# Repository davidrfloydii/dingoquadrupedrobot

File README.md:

# dingoquadrupedrobot
Modifications to Dingo Quadruped Robot

## [KiCAD PCB](https://github.com/davidrfloydii/dingoquadrupedrobot/tree/main/PCB)
Since the original files were Altium designer I recreated the board in KiCAD. Not 100% the same since it uses through hole components for the resistors and the diode.

## [Modified Base Plate](https://github.com/davidrfloydii/dingoquadrupedrobot/blob/main/CAD/Dingo%20Base%20Plate.step)
Instead of ordering the Acrylic pieces you can try to print your own base plates. **Note**: This is not verified to hold up to the stresses of the robot. However if you decide to go this route be sure to use 100% infill for these pieces. Also blue the two halves together. Since it is printed this will have stand offs for 2 of the Raspberry Pi mounts and the rear of the front buck converter.

## [Redesigned LCD Bracket](https://github.com/davidrfloydii/dingoquadrupedrobot/blob/main/CAD/Rear%20LCD%20Holder%20v1.step)
For my build I decided to redesign the rear LCD holder so that screws and nuts weren't positioning. **Note** This still has not been tested and results may vary depending on your printer settings.

## [New nose piece](https://github.com/davidrfloydii/dingoquadrupedrobot/blob/main/CAD/Dingo%20Front%20With%20Sonar%20v1.step)
The first modificaiton was to the front of the Dingo robot, it removes the plastic black eye and instead makes room for two HC-SR04 sensors.

## [New Fan Housing](https://github.com/davidrfloydii/dingoquadrupedrobot/blob/main/CAD/Fan%20Housings%20Builtin%20Hinge%20Pins.step)
This new fan housing creates tabs to act as the hinge. Reduces the number of pieces that need to be ordered.

## [Revised IMU Mount]((https://github.com/davidrfloydii/dingoquadrupedrobot/blob/main/CAD//Revised%20IMU%20Mount%20v4.step)
I updated the IMU mount because the version I ordered here in the US had slightly different pattern for mounting holes. Additionally the 3 digit display I ordered from Amazon also had slightly different mounting holes. If you are using the same components you can use this step file.

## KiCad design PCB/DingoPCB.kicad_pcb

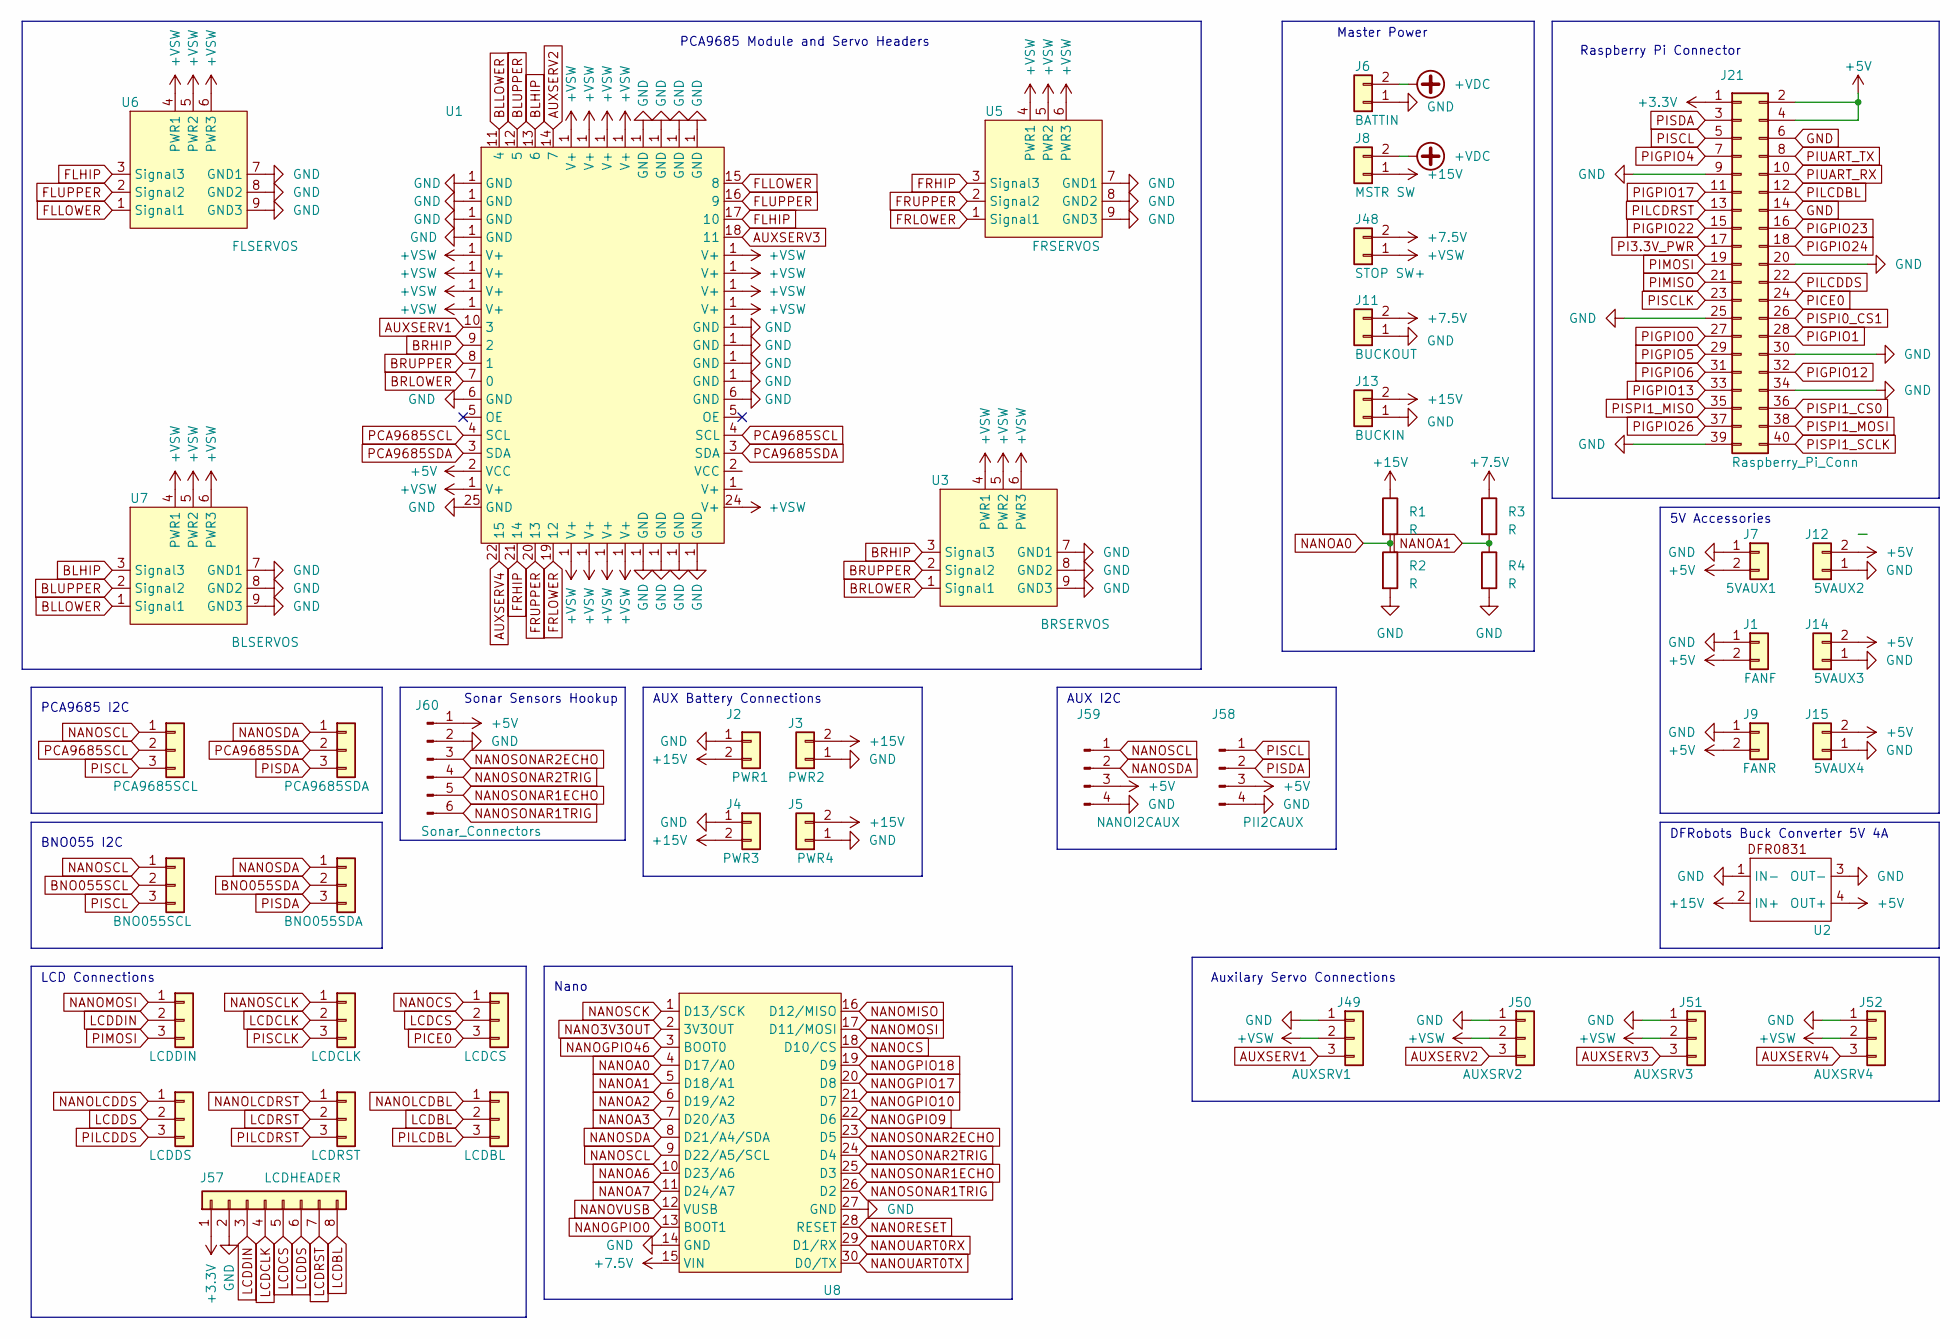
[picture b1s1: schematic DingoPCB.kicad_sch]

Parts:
J1: FANF; JST_EH_B2B-EH-A_1x02_P2.50mm_Vertical
J2: PWR1; TerminalBlock_Phoenix_MKDS-1,5-2-5.08_1x02_P5.08mm_Horizont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
J3: PWR2; TerminalBlock_Phoenix_MKDS-1,5-2-5.08_1x02_P5.08mm_Horizont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
J4: PWR3; TerminalBlock_Phoenix_MKDS-1,5-2-5.08_1x02_P5.08mm_Horizont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
J5: PWR4; TerminalBlock_Phoenix_MKDS-1,5-2-5.08_1x02_P5.08mm_Horizont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
J6: BATTIN; TerminalBlock_Phoenix_MKDS-1,5-2-5.08_1x02_P5.08mm_Horizont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
J7: 5VAUX1; JST_EH_B2B-EH-A_1x02_P2.50mm_Vertical
J8: MSTR SW; TerminalBlock_Phoenix_MKDS-1,5-2-5.08_1x02_P5.08mm_Horizont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
J9: FANR; JST_EH_B2B-EH-A_1x02_P2.50mm_Vertical
J10: PCA9685SDA; PinHeader_1x03_P2.54mm_Vertical
J11: BUCKOUT; TerminalBlock_Phoenix_MKDS-1,5-2-5.08_1x02_P5.08mm_Horizont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
J12: 5VAUX2; JST_EH_B2B-EH-A_1x02_P2.50mm_Vertical
J13: BUCKIN; TerminalBlock_Phoenix_MKDS-1,5-2-5.08_1x02_P5.08mm_Horizont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
J14: 5VAUX3; JST_EH_B2B-EH-A_1x02_P2.50mm_Vertical
J15: 5VAUX4; JST_EH_B2B-EH-A_1x02_P2.50mm_Vertical
J16: BNO055SDA; PinHeader_1x03_P2.54mm_Vertical
J17: BNO055SCL; PinHeader_1x03_P2.54mm_Vertical
J18: LCDDS; PinHeader_1x03_P2.54mm_Vertical
J19: LCDRST; PinHeader_1x03_P2.54mm_Vertical
J20: LCDBL; PinHeader_1x03_P2.54mm_Vertical
J21: Raspberry_Pi_Conn; PinHeader_2x20_P2.54mm_Vertical
J48: STOP SW+; TerminalBlock_Phoenix_MKDS-1,5-2-5.08_1x02_P5.08mm_Horizont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
J49: AUXSRV1; PinHeader_1x03_P2.54mm_Vertical
J50: AUXSRV2; PinHeader_1x03_P2.54mm_Vertical
J51: AUXSRV3; PinHeader_1x03_P2.54mm_Vertical
J52: AUXSRV4; PinHeader_1x03_P2.54mm_Vertical
J53: PCA9685SCL; PinHeader_1x03_P2.54mm_Vertical
J54: LCDDIN; PinHeader_1x03_P2.54mm_Vertical
J55: LCDCLK; PinHeader_1x03_P2.54mm_Vertical
J56: LCDCS; PinHeader_1x03_P2.54mm_Vertical
J57: LCDHEADER; PinHeader_1x08_P2.54mm_Horizontal
J58: PII2CAUX; JST_EH_B4B-EH-A_1x04_P2.50mm_Vertical
J59: NANOI2CAUX; JST_EH_B4B-EH-A_1x04_P2.50mm_Vertical
J60: Sonar_Connectors; JST_EH_B6B-EH-A_1x06_P2.50mm_Vertical
R1, R2, R3, R4: R; R_Axial_DIN0204_L3.6mm_D1.6mm_P2.54mm_Vertical
U1: Adafruit PCA9685 rev C
U2: DFR0831
U3: BRSERVOS; Three_Servo_Footprint
U5: FRSERVOS; Three_Servo_Footprint
U6: FLSERVOS; Three_Servo_Footprint
U7: BLSERVOS; Three_Servo_Footprint
U8: Arduino_Nano_ESP32

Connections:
+3.3V: J21.1, J57.1
+5V: J1.2, J7.2, J9.2, J12.2, J14.2, J15.2, J21.2, J21.4, J58.3, J59.3, J60.1, U1.2 (VCC), U2.4 (OUT+); also elsewhere on the board
+7.5V: J11.2, J48.2, R3.1, U8.15 (VIN)
+15V: J2.2, J3.2, J4.2, J5.2, J8.1, J13.2, R1.1, U2.2 (IN+)
+VDC: J6.2, J8.2
AUXSERV1: J49.3, U1.10 (3)
AUXSERV2: J50.3, U1.14 (7)
AUXSERV3: J51.3, U1.18 (11)
AUXSERV4: J52.3, U1.22 (15)
BLHIP: U1.13 (6), U7.3 (Signal3)
BLLOWER: U1.11 (4), U7.1 (Signal1)
BLUPPER: U1.12 (5), U7.2 (Signal2)
BNO055SCL: J17.2; also elsewhere on the board
BNO055SDA: J16.2; also elsewhere on the board
BRHIP: U1.9 (2), U3.3 (Signal3)
BRLOWER: U1.7 (0), U3.1 (Signal1)
BRUPPER: U1.8 (1), U3.2 (Signal2)
FLHIP: U1.17 (10), U6.3 (Signal3)
FLLOWER: U1.15 (8), U6.1 (Signal1)
FLUPPER: U1.16 (9), U6.2 (Signal2)
FRHIP: U1.21 (14), U5.3 (Signal3)
FRLOWER: U1.19 (12), U5.1 (Signal1)
FRUPPER: U1.20 (13), U5.2 (Signal2)
LCDBL: J20.2, J57.8
LCDCLK: J55.2, J57.4
LCDCS: J56.2, J57.5
LCDDIN: J54.2, J57.3
LCDDS: J18.2, J57.6
LCDRST: J19.2, J57.7
NANO3V3OUT: U8.2 (3V3OUT)
NANOA0: R1.2, R2.1, U8.4 (D17/A0)
NANOA1: R3.2, R4.1, U8.5 (D18/A1)
NANOA2: U8.6 (D19/A2)
NANOA3: U8.7 (D20/A3)
NANOA6: U8.10 (D23/A6)
NANOA7: U8.11 (D24/A7)
NANOCS: J56.1, U8.18 (D10/CS)
NANOGPIO0: U8.13 (BOOT1)
NANOGPIO9: U8.22 (D6)
NANOGPIO10: U8.21 (D7)
NANOGPIO17: U8.20 (D8)
NANOGPIO18: U8.19 (D9)
NANOGPIO46: U8.3 (BOOT0)
NANOLCDBL: J20.1
NANOLCDDS: J18.1
NANOLCDRST: J19.1
NANOMISO: U8.16 (D12/MISO)
NANOMOSI: J54.1, U8.17 (D11/MOSI)
NANORESET: U8.28 (RESET)
NANOSCK: U8.1 (D13/SCK)
NANOSCL: J17.1, J53.1, J59.1, U8.9 (D22/A5/SCL)
NANOSCLK: J55.1
NANOSDA: J10.1, J16.1, J59.2, U8.8 (D21/A4/SDA)
NANOSONAR1ECHO: J60.5, U8.25 (D3)
NANOSONAR1TRIG: J60.6, U8.26 (D2)
NANOSONAR2ECHO: J60.3, U8.23 (D5)
NANOSONAR2TRIG: J60.4, U8.24 (D4)
NANOUART0RX: U8.29 (D1/RX)
NANOUART0TX: U8.30 (D0/TX)
NANOVUSB: U8.12 (VUSB)
PCA9685SCL: J53.2, U1.4 (SCL)
PCA9685SDA: J10.2, U1.3 (SDA)
PI3.3V_PWR: J21.17
PICE0: J21.24, J56.3
PIGPIO0: J21.27
PIGPIO1: J21.28
PIGPIO4: J21.7
PIGPIO5: J21.29
PIGPIO6: J21.31
PIGPIO12: J21.32
PIGPIO13: J21.33
PIGPIO17: J21.11
PIGPIO22: J21.15
PIGPIO23: J21.16
PIGPIO24: J21.18
PIGPIO26: J21.37
PILCDBL: J20.3, J21.12
PILCDDS: J18.3, J21.22
PILCDRST: J19.3, J21.13
PIMISO: J21.21
PIMOSI: J21.19, J54.3
PISCL: J17.3, J21.5, J53.3, J58.1
PISCLK: J21.23, J55.3
PISDA: J10.3, J16.3, J21.3, J58.2
PISPI0_CS1: J21.26
PISPI1_CS0: J21.36
PISPI1_MISO: J21.35
PISPI1_MOSI: J21.38
PISPI1_SCLK: J21.40
PIUART_RX: J21.10
PIUART_TX: J21.8

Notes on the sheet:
Nano
PCA9685 I2C
5V Accessories
LCD Connections
AUX Battery Connections
PCA9685 Module and Servo Headers
AUX I2C
Sonar Sensors Hookup
Auxilary Servo Connections
Master Power
BNO055 I2C
DFRobots Buck Converter 5V 4A
Raspberry Pi Connector

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
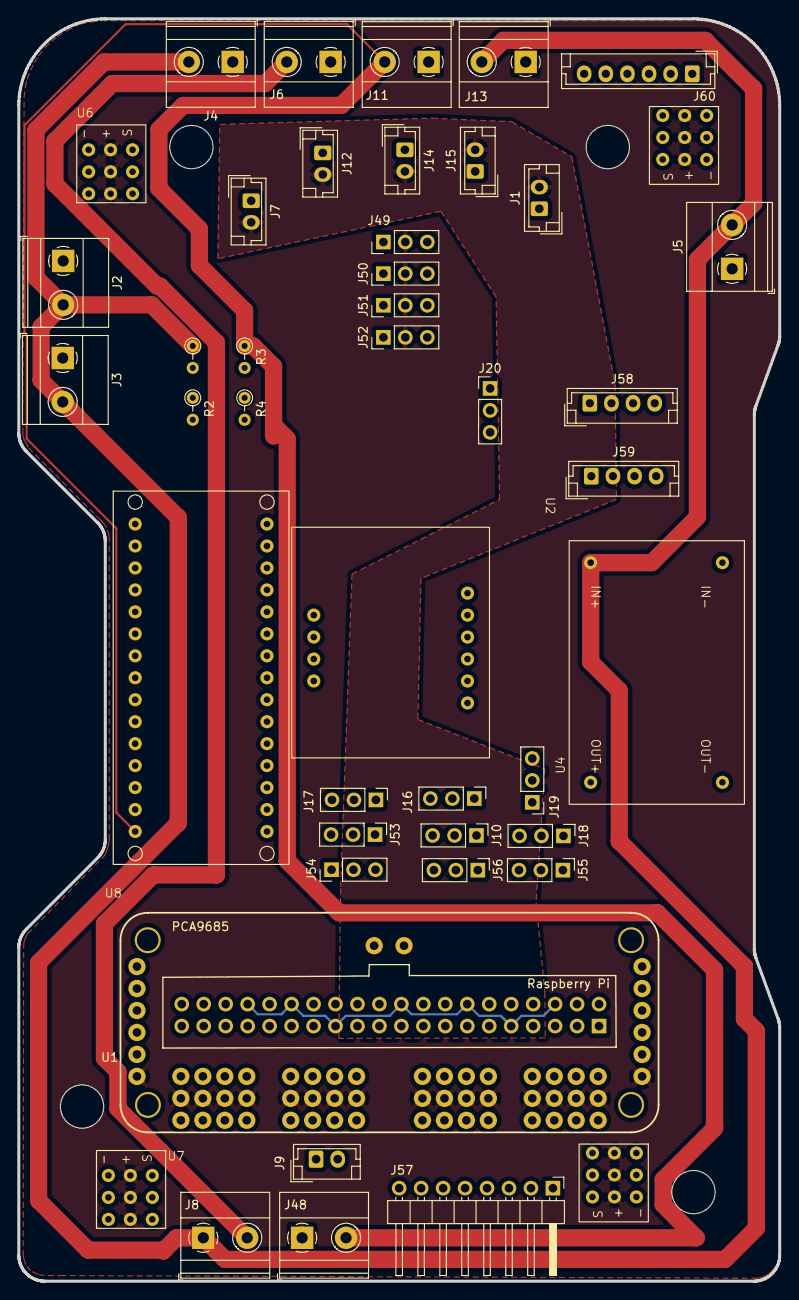
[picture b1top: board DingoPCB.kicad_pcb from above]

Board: 4 copper layers, 88.0 x 146.0 mm, 46 parts (1 on the bottom side), 51 nets.

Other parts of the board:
U4: Adafruit BNO055

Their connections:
+5V: U4.1 (+5V); also elsewhere on the board
BNO055SCL: U4.5 (SCL); also elsewhere on the board
BNO055SDA: U4.4 (SDA); also elsewhere on the board

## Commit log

2023-08-05 Adding step file for updated nose
    This new nose piece is designed to have a HC-SR04 module on each of the angled sides of the front. The black center eye piece has been removed to make room.
2023-08-05 Update README.md
    Added details for update STEP file
2023-08-07 Printable Version Base Plate
    The design calls for this piece to be cut in acrylic. I've cut the piece into two pieces then created overlap so that there is some strength where the pieces come together. Printed with ABS at 100% i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
2023-08-07 Fan holders with built in hinge pins
    The original design printed the fan holders with the assumption that another piece would be used to form the hinge. I am trying this to see if printing with the pins built in will fit nicely and hold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
2023-08-08 Top plate of robot split in half with overlap
    My printer was not large enough to print this in one piece. I modified the part to split it in half then overlap tabs on each side for a strong connection between the two pieces. If you want to glue 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
2023-08-08 Image of new fan housing design
    This is the design of the new fan housing
2023-08-09 Restructuring directory
2023-08-09 Adding KiCAD for PCB
2023-08-09 Updates to masks on PCB
2023-08-09 Gerber files added
2023-08-09 Updating image of PCB
2023-08-09 Updating image again.
2023-08-09 Updated PCB Export
2023-08-09 Updates to PCB for better readability
2023-08-09 Moved terminals closer together
2023-08-09 Updated 3D image of PCB
2023-08-10 Adding redesigned LCD holder
2023-08-10 Adding photo to readme
2023-08-11 Updated PCB exports and rear screen holder
2023-08-11 Updated base plate step file and image of new design.
2023-08-11 Adding version of rear LCD mount that I am using
2023-08-11 Testing hyperlink
2023-08-11 Testing again
2023-08-11 Adding link for base plate
2023-08-11 More link updates and removing old file
2023-08-11 More link updates
2023-08-11 Fixing link
2023-08-12 Revised IMU mount for amazon parts
2023-08-19 Latest revisions to all CAD and updated PCB
2023-08-19 Adding script used to setup Ubuntu and ROS Noetic
2023-10-12 Adding updated servo carriers
